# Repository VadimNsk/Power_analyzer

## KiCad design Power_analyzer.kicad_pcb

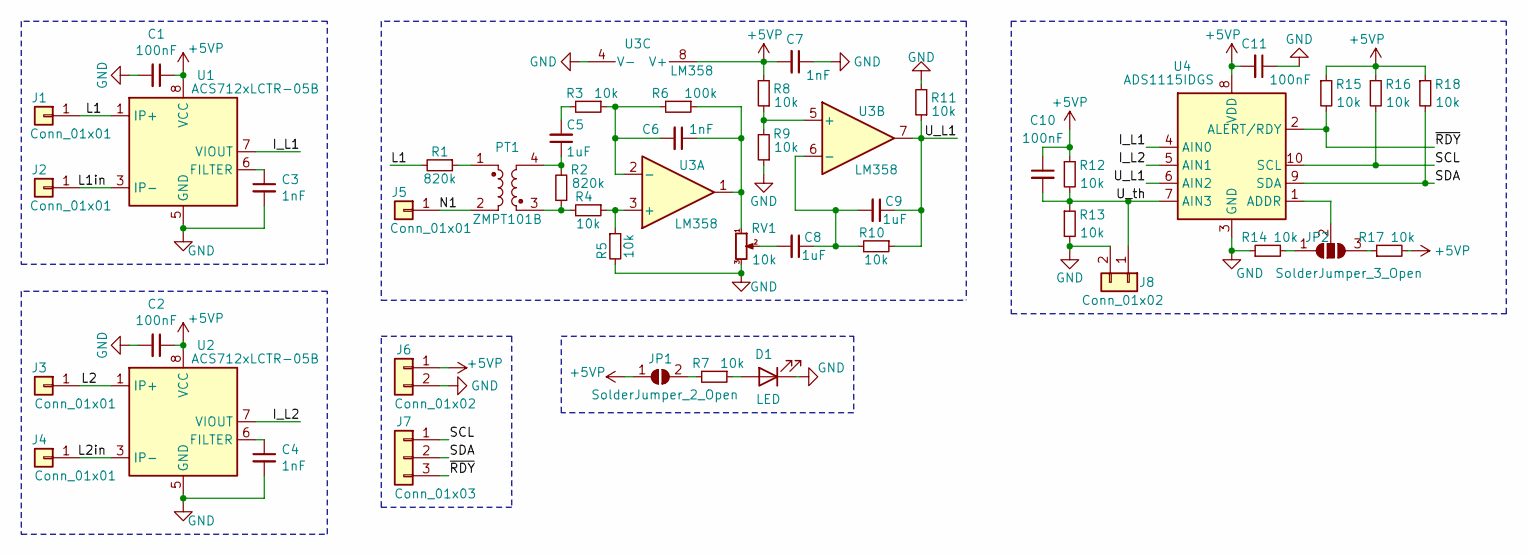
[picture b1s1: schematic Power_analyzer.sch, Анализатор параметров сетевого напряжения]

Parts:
C1, C2, C10, C11: 100nF; C_0603_1608Metric
C3, C4, C6, C7: 1nF; C_0603_1608Metric
C5, C8, C9: 1uF; C_0603_1608Metric
D1: LED; LED_D2.0mm_W4.8mm_H2.5mm_FlatTop
J1, J2, J3, J4, J5: Conn_01x01; PinHeader_1x01_P2.54mm
J6: Conn_01x02; PinHeader_1x02_P2.54mm
J7: Conn_01x03; PinHeader_1x03_P2.54mm
J8: Conn_01x02; JST_EH_B2B-EH-A_1x02_P2.50mm_Vertical
JP1: SolderJumper_2_Open; SolderJumper-2_P1.3mm_Open_RoundedPad1.0x1.5mm
JP2: SolderJumper_3_Open; SolderJumper-3_P2.0mm_Open_TrianglePad1.0x1.5mm
PT1: ZMPT101B; ZMPT101B2
R1: 820k; R_Axial_DIN0309_L9.0mm_D3.2mm_P5.08mm_Vertical
R2: 820k; R_0603_1608Metric
R3, R4, R5, R7, R8, R9, R10, R11, R12, R13, R14, R15, R16, R17, R18: 10k; R_0603_1608Metric
R6: 100k; R_0603_1608Metric
RV1: 10k; Potentiometer_Bourns_3296W_Vertical
U1, U2: ACS712xLCTR-05B; SOIC-8_3.9x4.9mm_P1.27mm
U3: LM358; SOIC-8_3.9x4.9mm_P1.27mm
U4: ADS1115IDGS; TSSOP-10_3x3mm_P0.5mm

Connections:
+5VP: C1.1, C2.1, C7.2, C10.1, C11.2, J6.1, JP1.1 (A), R8.2, R12.1, R15.1, R16.1, R17.2, R18.1, U1.8 (VCC), U2.8 (VCC), U3.8 (V+), U4.8 (VDD)
/I_L1: U1.7 (VIOUT), U4.4 (AIN0)
/I_L2: U2.7 (VIOUT), U4.5 (AIN1)
/L1: J1.1, R1.2, U1.1 (IP+), U1.2 (IP+)
/L1in: J2.1, U1.3 (IP-), U1.4 (IP-)
/L2: J3.1, U2.1 (IP+), U2.2 (IP+)
/L2in: J4.1, U2.3 (IP-), U2.4 (IP-)
/N1: J5.1, PT1.2
/SCL: J7.1, R16.2, U4.10 (SCL)
/SDA: J7.2, R18.2, U4.9 (SDA)
/U_L1: C9.1, R10.1, R11.1, U3.7, U4.6 (AIN2)
/U_th: C10.2, J8.1, R12.2, R13.1, U4.7 (AIN3)
/~RDY: J7.3, R15.2, U4.2 (ALERT/RDY)
GND: C1.2, C2.2, C3.2, C4.2, C7.1, C11.1, D1.1 (K), J6.2, J8.2, R5.2, R9.1, R11.2, R13.2, R14.1, RV1.3, U1.5 (GND), U2.5 (GND), U3.4 (V-), U4.3 (GND)
unnamed: C3.1, U1.6 (FILTER)
unnamed: C4.1, U2.6 (FILTER)
unnamed: C5.1, PT1.4, R2.2
unnamed: C5.2, R3.2
unnamed: C6.1, R6.1, RV1.1, U3.1
unnamed: C6.2, R3.1, R6.2, U3.2 (-)
unnamed: C8.1, C9.2, R10.2, U3.6 (-)
unnamed: C8.2, RV1.2
unnamed: D1.2 (A), R7.1
unnamed: JP1.2 (B), R7.2
unnamed: JP2.1 (A), R14.2
unnamed: JP2.2 (C), U4.1 (ADDR)
unnamed: JP2.3 (B), R17.1
unnamed: PT1.1, R1.1
unnamed: PT1.3, R2.1, R4.2
unnamed: R4.1, R5.1, U3.3 (+)
unnamed: R8.1, R9.2, U3.5 (+)

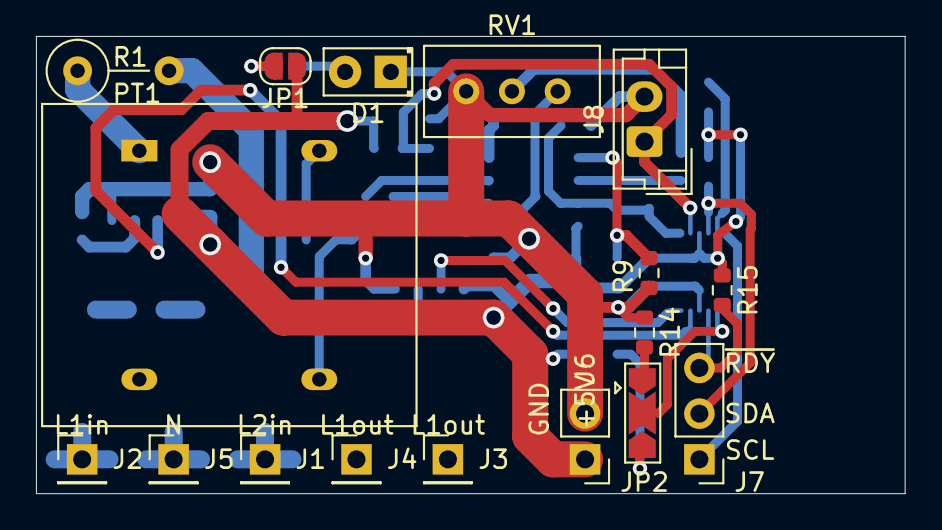
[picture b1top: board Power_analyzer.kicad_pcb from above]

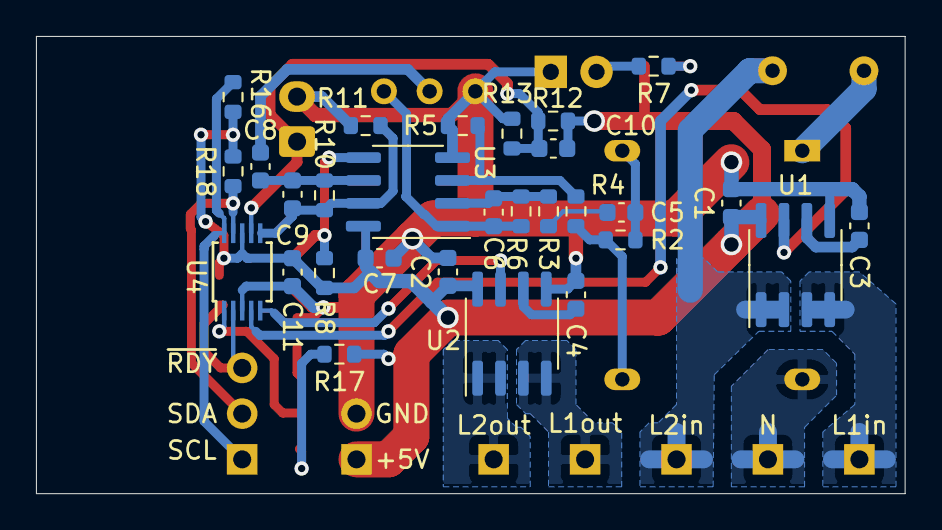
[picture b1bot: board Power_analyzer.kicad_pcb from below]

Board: 2 copper layers, 48.3 x 25.4 mm, 46 parts (29 on the bottom side), 31 nets.

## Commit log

2020-12-04 ????? ????????? ??????? ???????? ??? ?????? ? ??????, ?????? ????????? ?????, ???????? ??? ???? ????? ??????? ? ???????? ????????????? ??? ?????? ????????? ??????? +5?.
